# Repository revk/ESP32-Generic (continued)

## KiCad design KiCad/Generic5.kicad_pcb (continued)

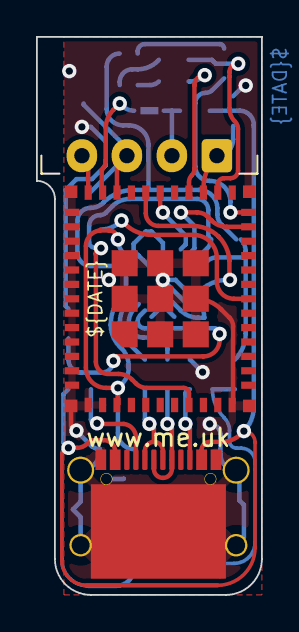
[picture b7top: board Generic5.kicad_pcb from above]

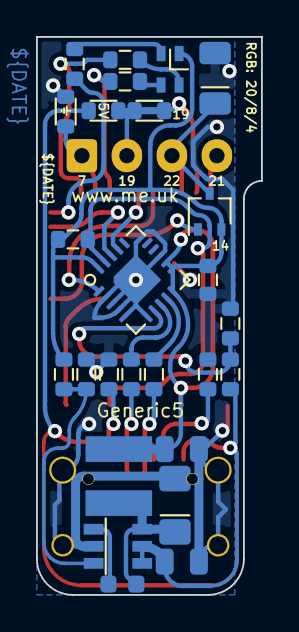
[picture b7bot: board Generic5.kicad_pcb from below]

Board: 2 copper layers, 12.5 x 31.0 mm, 29 parts (26 on the bottom side), 27 nets.
